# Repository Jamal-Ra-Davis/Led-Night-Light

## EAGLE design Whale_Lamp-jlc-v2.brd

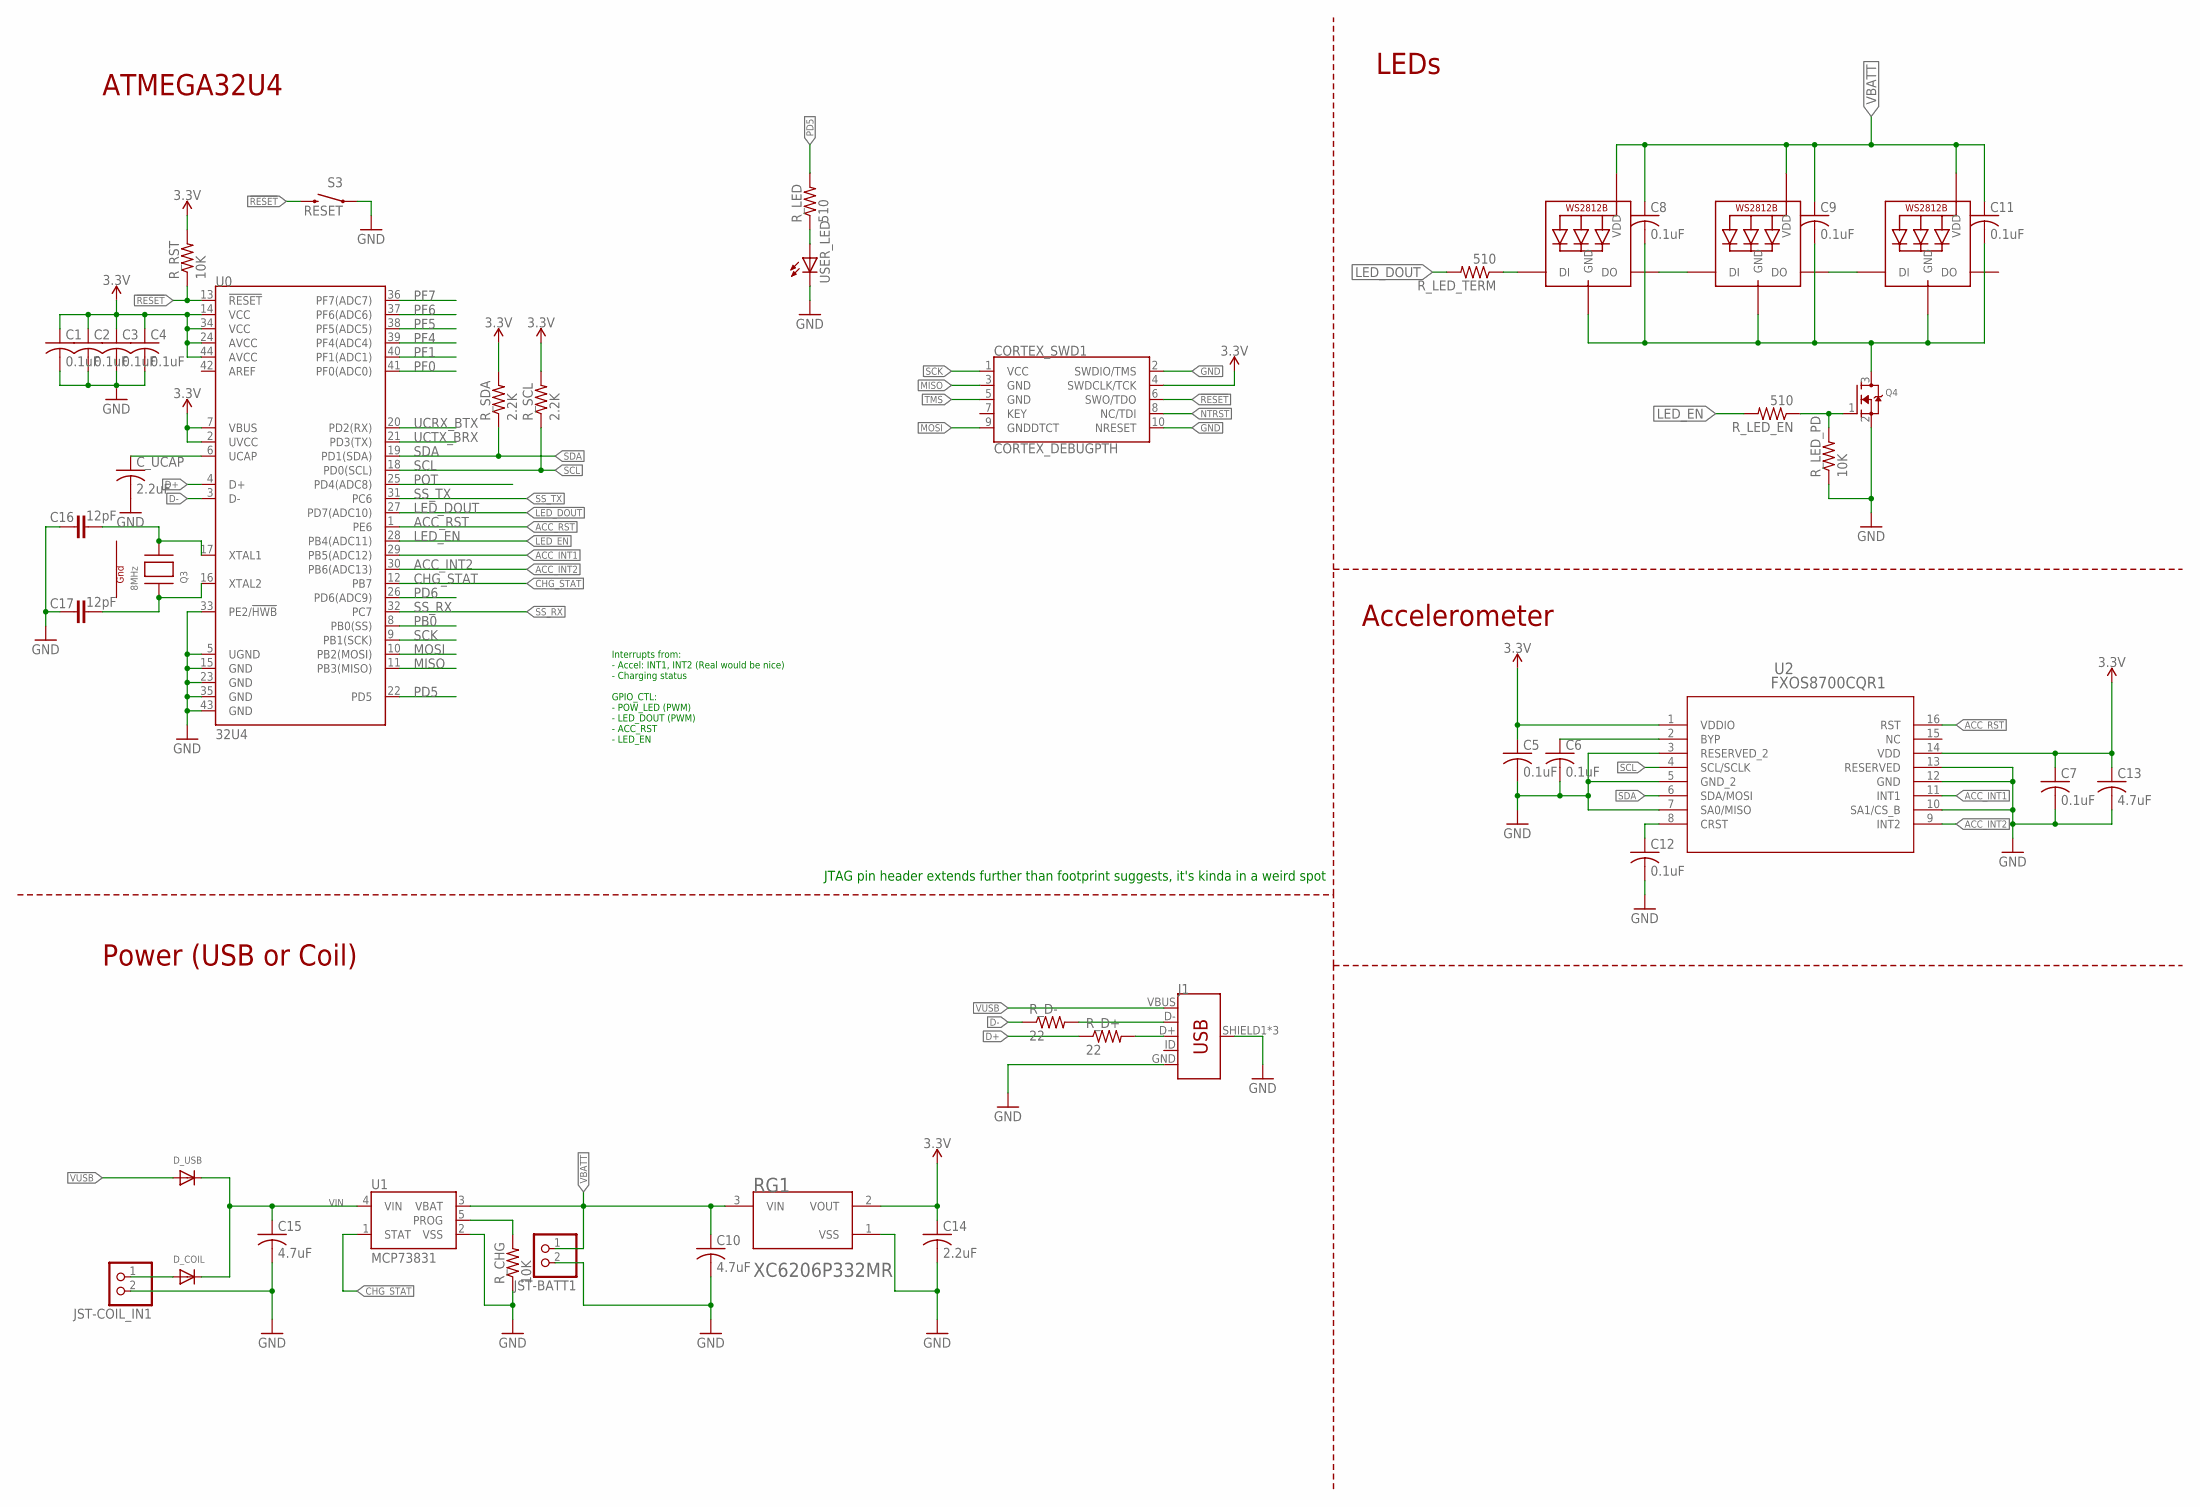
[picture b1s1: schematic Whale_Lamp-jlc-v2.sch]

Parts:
C1, C2, C3, C4, C5, C6, C7, C8, C9, C11, C12: 0.1uF; C0402
C10, C13, C15: 4.7uF; C0603
C14: 2.2uF; C0603
C16, C17: 12pF; 0402-CAP
CORTEX_SWD1: CORTEX_DEBUGPTH; 2X5-PTH-1.27MM
C_UCAP: 2.2uF; C0603
D_COIL: DIODESOD-123; SOD-123
D_USB: DIODESOD-123; SOD-123
J1: USB_MICRO-B_FEMALE-SMT; USB-B-MICRO-SMD
JST-BATT1: JST_2PIN-THM-RA; JST-PH-2-THM-RA
JST-COIL_IN1: JST_2PIN-THM-RA; JST-PH-2-THM-RA
LED1, LED2, LED3: WS2812B3535; LED3535
Q3: 8MHz; NX3225
Q4: MOSFET-NREFLOW; SOT23
RG1: TOREX_XC6206P332MRTOREX_XC6206P332MR_0_0; TOREX_XC6206P332MR_0
R_CHG: 10K; R0402
R_D+: 22; R0402
R_D-: 22; R0402
R_LED: 510; R0402
R_LED_EN: 510; R0402
R_LED_PD: 10K; R0402
R_LED_TERM: 510; R0402
R_RST: 10K; R0402
R_SCL: 2.2K; R0402
R_SDA: 2.2K; R0402
S3: RESET; TACTILE_SWITCH_SMD_4.6X2.8MM
U0: 32U4; QFN-44
U1: MCP73831; SOT23-5
U2: FXOS8700CQR1; QFN16_3X3_NXP
USER_LED: LEDCHIPLED_0603; CHIPLED_0603

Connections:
3.3V: C1.1, C2.1, C3.1, C4.1, C5.1, C7.1, C13.1, C14.1, CORTEX_SWD1.4 (SWDCLK/TCK), RG1.2 (VOUT), R_RST.2, R_SCL.2, R_SDA.2, U0.2 (UVCC), U0.7 (VBUS), U0.14 (VCC), U0.24 (AVCC), U0.34 (VCC), U0.44 (AVCC), U2.1 (VDDIO), U2.14 (VDD)
!RESET: CORTEX_SWD1.6 (SWO/TDO), R_RST.1, S3.3 (2), S3.4 (2), U0.13 (!RESET)
ACC_INT1: U0.29 (PB5(ADC12)), U2.11 (INT1)
ACC_INT2: U0.30 (PB6(ADC13)), U2.9 (INT2)
ACC_RST: U0.1 (PE6), U2.16 (RST)
CHG_STAT: U0.12 (PB7), U1.1 (STAT)
D+: R_D+.1, U0.4 (D+)
D-: R_D-.1, U0.3 (D-)
G1: Q3.4 (G1)
G2: Q3.2 (G2)
GND: C1.2, C2.2, C3.2, C4.2, C5.2, C6.2, C7.2, C10.2, C12.2, C13.2, C14.2, C15.2, C16.1, C17.1, CORTEX_SWD1.2 (SWDIO/TMS), CORTEX_SWD1.10 (NRESET), C_UCAP.2, J1.GND, J1.SHIELD1 (SHIELD), J1.SHIELD2 (SHIELD), J1.SHIELD3 (SHIELD), JST-BATT1.2 (1), JST-COIL_IN1.2 (1), Q4.2 (S), RG1.1 (VSS), R_CHG.1, R_LED_PD.1, S3.1, S3.2 (1), U0.5 (UGND), U0.15 (GND), U0.23 (GND), U0.33 (PE2/!HWB), U0.35 (GND), U0.43 (GND), U1.2 (VSS), U2.3 (RESERVED_2), U2.5 (GND_2), U2.7 (SA0/MISO), U2.10 (SA1/CS_B), U2.12 (GND), U2.13 (RESERVED), USER_LED.C
LED_DOUT: R_LED_TERM.2, U0.27 (PD7(ADC10))
LED_EN: R_LED_EN.2, U0.28 (PB4(ADC11))
MISO: CORTEX_SWD1.3 (GND), U0.11 (PB3(MISO))
MOSI: CORTEX_SWD1.9 (GNDDTCT), U0.10 (PB2(MOSI))
unnamed: J1.D-, R_D-.2
unnamed: R_CHG.2, U1.5 (PROG)
unnamed: R_LED.1, USER_LED.A
unnamed: C16.2, Q3.3 (X2), U0.17 (XTAL1)
unnamed: C17.2, Q3.1 (X1), U0.16 (XTAL2)
unnamed: LED1.3 (DO), LED2.1 (DI)
unnamed: LED2.3 (DO), LED3.1 (DI)
unnamed: C8.2, C9.2, C11.2, LED1.4 (GND), LED2.4 (GND), LED3.4 (GND), Q4.3 (D)
unnamed: LED1.1 (DI), R_LED_TERM.1
unnamed: Q4.1 (G), R_LED_EN.1, R_LED_PD.2
unnamed: C12.1, U2.8 (CRST)
unnamed: C6.1, U2.2 (BYP)
unnamed: C_UCAP.1, U0.6 (UCAP)
unnamed: J1.D+, R_D+.2
unnamed: D_COIL.A, JST-COIL_IN1.1 (2)
NTRST: CORTEX_SWD1.8 (NC/TDI)
PB0: U0.8 (PB0(SS))
PD5: R_LED.2, U0.22 (PD5)
PD6: U0.26 (PD6(ADC9))
PF0: U0.41 (PF0(ADC0))
PF1: U0.40 (PF1(ADC1))
PF4: U0.39 (PF4(ADC4))
PF5: U0.38 (PF5(ADC5))
PF6: U0.37 (PF6(ADC6))
PF7: U0.36 (PF7(ADC7))
POT: U0.25 (PD4(ADC8))
SCK: CORTEX_SWD1.1 (VCC), U0.9 (PB1(SCK))
SCL: R_SCL.1, U0.18 (PD0(SCL)), U2.4 (SCL/SCLK)
SDA: R_SDA.1, U0.19 (PD1(SDA)), U2.6 (SDA/MOSI)
SS_RX: U0.32 (PC7)
SS_TX: U0.31 (PC6)
TMS: CORTEX_SWD1.5 (GND)
UCRX_BTX: U0.20 (PD2(RX))
UCTX_BRX: U0.21 (PD3(TX))
VBATT: C8.1, C9.1, C10.1, C11.1, JST-BATT1.1 (2), LED1.2 (VDD), LED2.2 (VDD), LED3.2 (VDD), RG1.3 (VIN), U1.3 (VBAT)
VIN: C15.1, D_COIL.C, D_USB.C, U1.4 (VIN)
VUSB: D_USB.A, J1.VBUS

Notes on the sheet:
LEDs
ATMEGA32U4
Power (USB or Coil)
Accelerometer
JTAG pin header extends further than footprint suggests, it's kinda in a weird spot
Interrupts from: - Accel: INT1, INT2 (Real would be nice) - Charging status GPIO_CTL: - POW_LED (PWM) - LED_DOUT (PWM) - ACC_RST - LED_EN

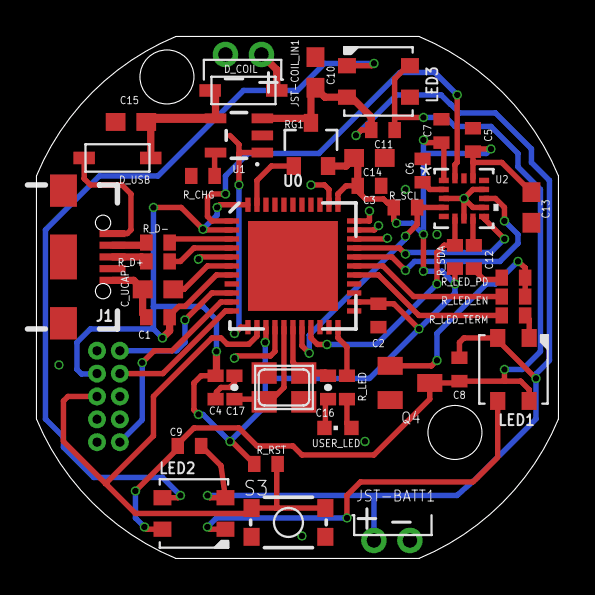
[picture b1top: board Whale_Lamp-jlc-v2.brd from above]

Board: 2 copper layers, 29.0 x 29.0 mm, 45 parts (1 on the bottom side), 35 nets.

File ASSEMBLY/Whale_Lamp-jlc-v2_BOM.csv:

Designator,Quantity,Value,Footprint,LCSC Part #
"D_COIL, D_USB",2,,SOD-123,C8598
USER_LED,1,,603,C72038 
Q4,1,,SOT-23-3L,C20917
Q3,1,,SMD-3225_4P ,C57131 
"C1, C2, C3, C4, C5, C6, C7, C8, C9, C11, C12",11,0.1uF,402,C1525 
"R_CHG, R_CHG_STAT, R_LED_PD, R_RST",4,10K,402,C25744 
"C16, C17",2,12pF,402,C1547 
"R_SCL, R_SDA",2,2.2K,402,C25879 
"C_UCAP, C14",2,2.2uF,603,C23630 
"R_D+, R_D-",2,22,402,C25092 
U0,1,32U4,QFN-44,C45874 
"C10, C13, C15",3,4.7uF,603,C19666 
"R_LED, R_LED_EN, R_LED_TERM",3,510,402,C25123 
U2,1,FXOS8700CQR1,QFN-16_3.0x3.0x0.5P,C432308 
U1,1,MCP73831,SOT23-5,C424093
RG1,1,TOREX_XC6206P332MRTOREX_XC6206P332MR_0_0,SOT-23-3L,C5446
"LED1, LED2, LED3",3,WS2812B3535,LED-4_3535,-

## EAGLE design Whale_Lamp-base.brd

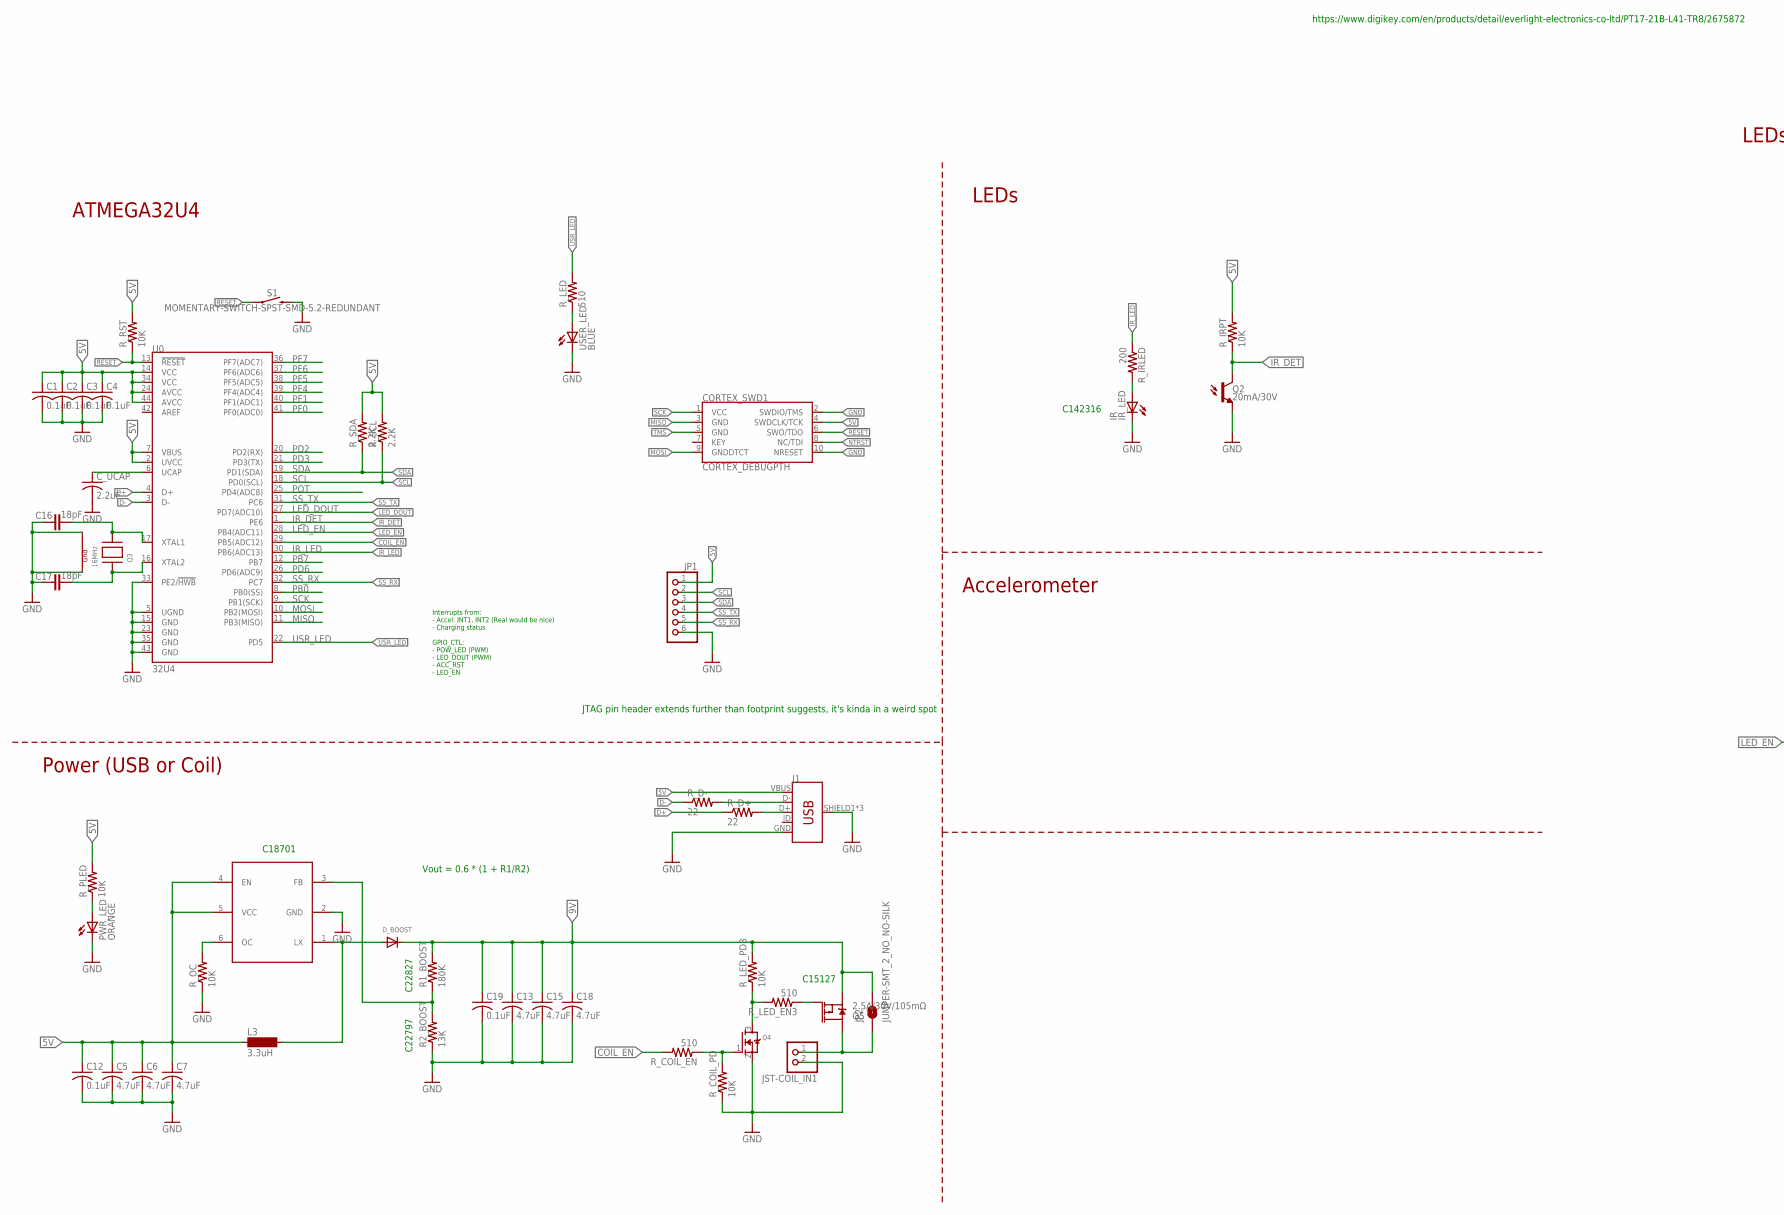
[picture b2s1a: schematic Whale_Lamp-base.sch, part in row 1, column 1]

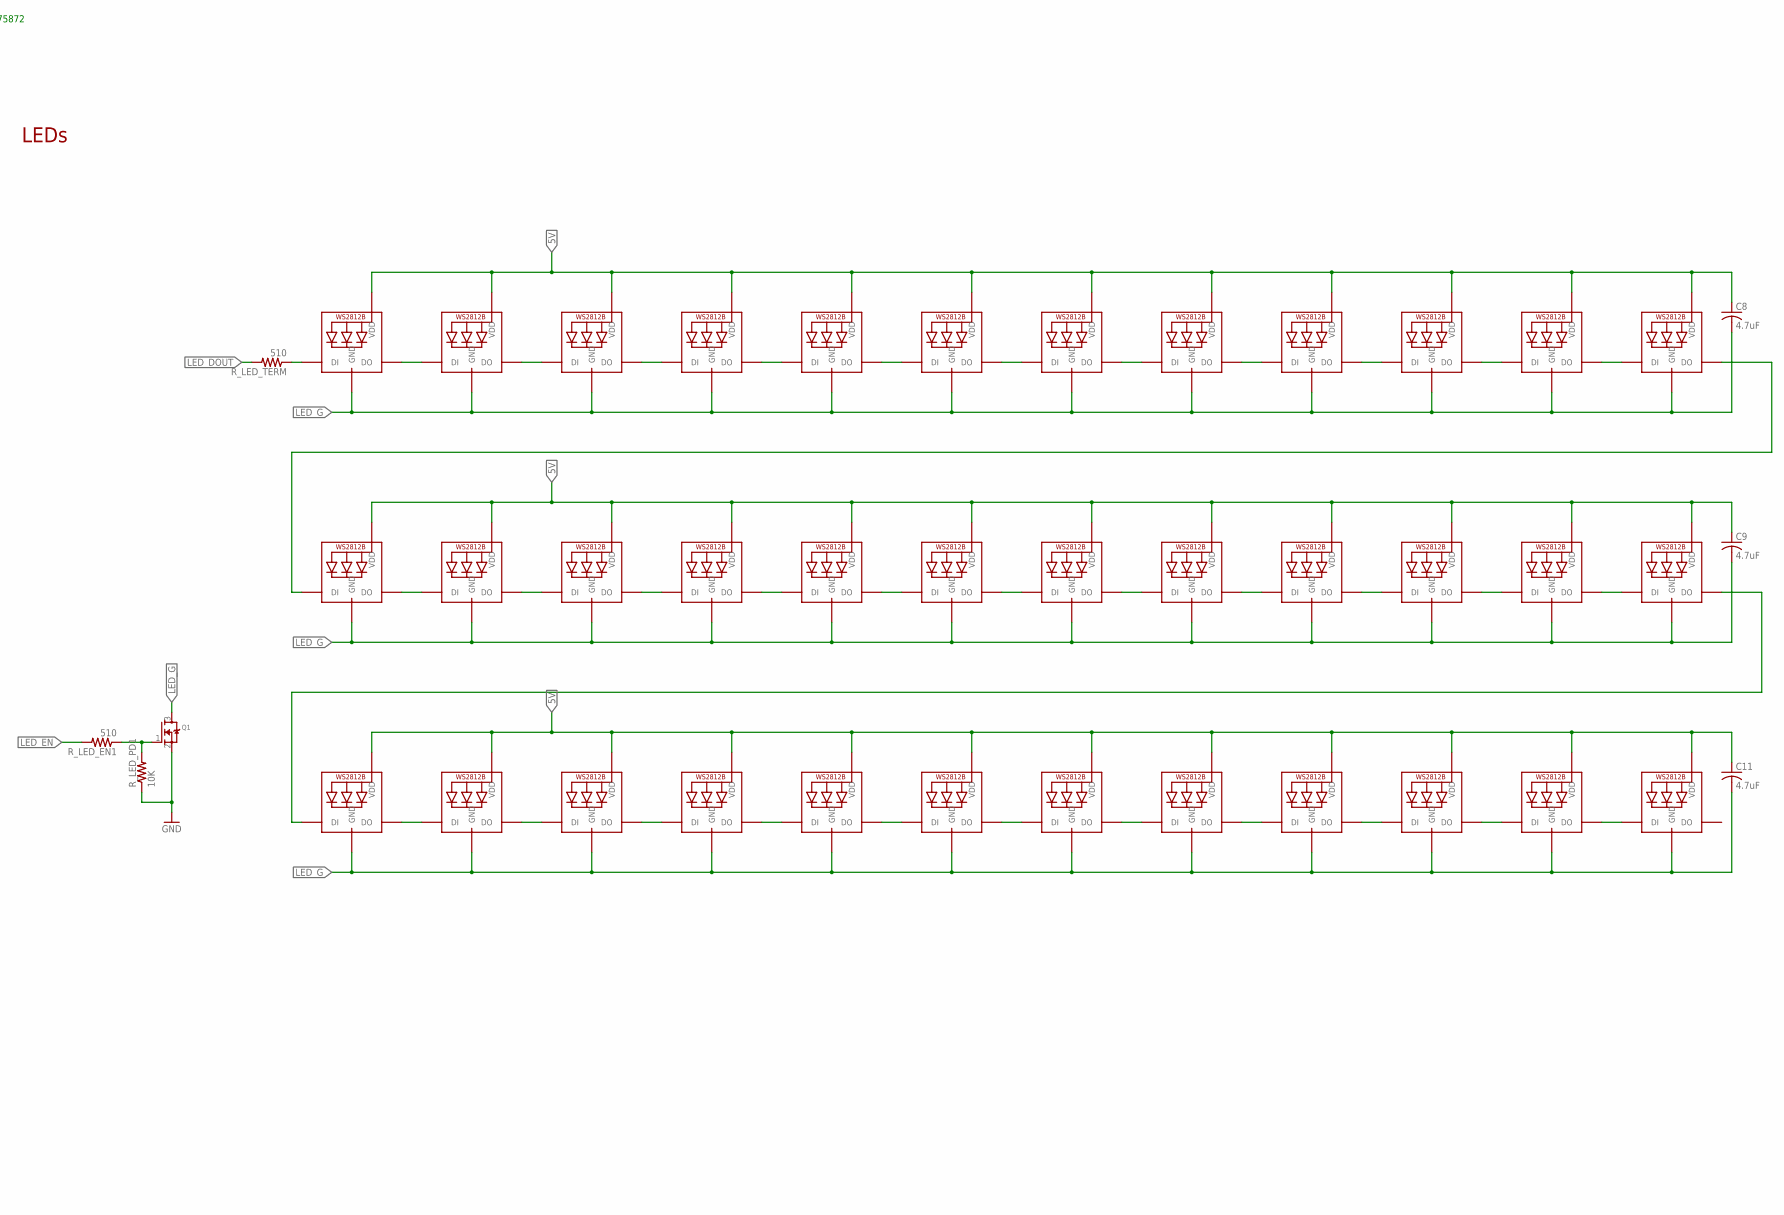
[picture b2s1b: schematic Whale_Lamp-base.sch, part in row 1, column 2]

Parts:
C1, C2, C3, C4, C12, C19: 0.1uF; C0402
C5, C6, C7, C8, C9, C11, C13, C15, C18: 4.7uF; C0603
C16, C17: 18pF; 0402-CAP
CORTEX_SWD1: CORTEX_DEBUGPTH; 2X5-PTH-1.27MM
C_UCAP: 2.2uF; C0603
D_BOOST: DIODESOD-123; SOD-123
FP6291: FP6291; SOT23-6L
IR_LED: IR; CHIPLED_0603
J1: USB_MICRO-B_FEMALE-SMT; USB-B-MICRO-SMD
JP1: PINHD-1X6; 1X06
JP2: JUMPER-SMT_2_NO_NO-SILK; SMT-JUMPER_2_NO_NO-SILK
JST-COIL_IN1: JST_2PIN-THM-RA; JST-PH-2-THM-RA
L3: 3.3uH; MS50
LED1, LED2, LED3, LED4, LED5, LED6, LED7, LED8, LED9, LED10, LED11, LED12, LED13, LED14, LED15, LED16, LED17, LED18, LED19, LED20, LED21, LED22, LED23, LED24, LED25, LED26, LED27, LED28, LED29, LED30, LED31, LED32, LED33, LED34, LED35, LED36: WS2812B_5050N; WS2812B-NARROW
PWR_LED: ORANGE; CHIPLED_0603
Q1, Q4: MOSFET-NREFLOW; SOT23
Q2: 20mA/30V; PT17-21C-L41-TR8
Q3: 16MHz; NX3225
Q5: 2.5A/30V/105mΩ; SOT23-3
R1_BOOST: 180K; R0603
R2_BOOST: 13K; R0603
R_COIL_EN: 510; R0402
R_COIL_PD: 10K; R0402
R_D+: 22; R0402
R_D-: 22; R0402
R_IRLED: 200; R0603
R_IRPT: 10K; R0402
R_LED: 510; R0402
R_LED_EN1, R_LED_EN3: 510; R0402
R_LED_PD1, R_LED_PD3: 10K; R0402
R_LED_TERM: 510; R0402
R_OC: 10K; R0402
R_PLED: 10K; R0402
R_RST: 10K; R0402
R_SCL: 2.2K; R0402
R_SDA: 2.2K; R0402
S1: MOMENTARY-SWITCH-SPST-SMD-5.2-REDUNDANT; TACTILE_SWITCH_SMD_5.2MM
U0: 32U4; QFN-44
USER_LED: BLUE; CHIPLED_0603

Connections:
5V: C1.1, C2.1, C3.1, C4.1, C5.1, C6.1, C7.1, C8.1, C9.1, C11.1, C12.1, CORTEX_SWD1.4 (SWDCLK/TCK), FP6291.4 (EN), FP6291.5 (VCC), J1.VBUS, JP1.1, L3.1, LED1.1-VDD (VDD), LED2.1-VDD (VDD), LED3.1-VDD (VDD), LED4.1-VDD (VDD), LED5.1-VDD (VDD), LED6.1-VDD (VDD), LED7.1-VDD (VDD), LED8.1-VDD (VDD), LED9.1-VDD (VDD), LED10.1-VDD (VDD), LED11.1-VDD (VDD), LED12.1-VDD (VDD), LED13.1-VDD (VDD), LED14.1-VDD (VDD), LED15.1-VDD (VDD), LED16.1-VDD (VDD), LED17.1-VDD (VDD), LED18.1-VDD (VDD), LED19.1-VDD (VDD), LED20.1-VDD (VDD), LED21.1-VDD (VDD), LED22.1-VDD (VDD), LED23.1-VDD (VDD), LED24.1-VDD (VDD), LED25.1-VDD (VDD), LED26.1-VDD (VDD), LED27.1-VDD (VDD), LED28.1-VDD (VDD), LED29.1-VDD (VDD), LED30.1-VDD (VDD), LED31.1-VDD (VDD), LED32.1-VDD (VDD), LED33.1-VDD (VDD), LED34.1-VDD (VDD), LED35.1-VDD (VDD), LED36.1-VDD (VDD), R_IRPT.2, R_PLED.2, R_RST.2, R_SCL.2, R_SDA.2, U0.2 (UVCC), U0.7 (VBUS), U0.14 (VCC), U0.24 (AVCC), U0.34 (VCC), U0.44 (AVCC)
9V: C13.1, C15.1, C18.1, C19.1, D_BOOST.C, JP2.2, Q5.2 (S), R1_BOOST.2, R_LED_PD3.2
!RESET: CORTEX_SWD1.6 (SWO/TDO), R_RST.1, S1.1, S1.2 (1), U0.13 (!RESET)
COIL_EN: R_COIL_EN.2, U0.29 (PB5(ADC12))
D+: R_D+.1, U0.4 (D+)
D-: R_D-.1, U0.3 (D-)
GND: C1.2, C2.2, C3.2, C4.2, C5.2, C6.2, C7.2, C12.2, C13.2, C15.2, C16.1, C17.1, C18.2, C19.2, CORTEX_SWD1.2 (SWDIO/TMS), CORTEX_SWD1.10 (NRESET), C_UCAP.2, FP6291.2 (GND), IR_LED.C, J1.GND, J1.SHIELD1 (SHIELD), J1.SHIELD2 (SHIELD), J1.SHIELD3 (SHIELD), JP1.6, JST-COIL_IN1.2 (1), PWR_LED.C, Q1.2 (S), Q2.E, Q3.2 (G2), Q3.4 (G1), Q4.2 (S), R2_BOOST.1, R_COIL_PD.1, R_LED_PD1.1, R_OC.1, S1.3 (2), S1.4 (2), U0.5 (UGND), U0.15 (GND), U0.23 (GND), U0.33 (PE2/!HWB), U0.35 (GND), U0.43 (GND), USER_LED.C
IR_DET: Q2.C, R_IRPT.1, U0.1 (PE6)
IR_LED: R_IRLED.1, U0.30 (PB6(ADC13))
LED_DOUT: R_LED_TERM.2, U0.27 (PD7(ADC10))
LED_EN: R_LED_EN1.2, U0.28 (PB4(ADC11))
LED_G: C8.2, C9.2, C11.2, LED1.3-GND (GND), LED2.3-GND (GND), LED3.3-GND (GND), LED4.3-GND (GND), LED5.3-GND (GND), LED6.3-GND (GND), LED7.3-GND (GND), LED8.3-GND (GND), LED9.3-GND (GND), LED10.3-GND (GND), LED11.3-GND (GND), LED12.3-GND (GND), LED13.3-GND (GND), LED14.3-GND (GND), LED15.3-GND (GND), LED16.3-GND (GND), LED17.3-GND (GND), LED18.3-GND (GND), LED19.3-GND (GND), LED20.3-GND (GND), LED21.3-GND (GND), LED22.3-GND (GND), LED23.3-GND (GND), LED24.3-GND (GND), LED25.3-GND (GND), LED26.3-GND (GND), LED27.3-GND (GND), LED28.3-GND (GND), LED29.3-GND (GND), LED30.3-GND (GND), LED31.3-GND (GND), LED32.3-GND (GND), LED33.3-GND (GND), LED34.3-GND (GND), LED35.3-GND (GND), LED36.3-GND (GND), Q1.3 (D)
MISO: CORTEX_SWD1.3 (GND), U0.11 (PB3(MISO))
MOSI: CORTEX_SWD1.9 (GNDDTCT), U0.10 (PB2(MOSI))
unnamed: LED1.2-DOUT (DO), LED2.4-DIN (DI)
unnamed: LED4.2-DOUT (DO), LED5.4-DIN (DI)
unnamed: LED5.2-DOUT (DO), LED6.4-DIN (DI)
unnamed: LED7.2-DOUT (DO), LED8.4-DIN (DI)
unnamed: LED8.2-DOUT (DO), LED9.4-DIN (DI)
unnamed: Q4.1 (G), R_COIL_EN.1, R_COIL_PD.2
unnamed: R_LED.1, USER_LED.A
unnamed: LED13.2-DOUT (DO), LED14.4-DIN (DI)
unnamed: C16.2, Q3.3 (X2), U0.17 (XTAL1)
unnamed: C17.2, Q3.1 (X1), U0.16 (XTAL2)
unnamed: LED14.2-DOUT (DO), LED15.4-DIN (DI)
unnamed: LED12.2-DOUT (DO), LED13.4-DIN (DI)
unnamed: LED16.2-DOUT (DO), LED17.4-DIN (DI)
unnamed: LED17.2-DOUT (DO), LED18.4-DIN (DI)
unnamed: LED19.2-DOUT (DO), LED20.4-DIN (DI)
unnamed: LED20.2-DOUT (DO), LED21.4-DIN (DI)
unnamed: LED21.2-DOUT (DO), LED22.4-DIN (DI)
unnamed: Q5.1 (G), R_LED_EN3.1
unnamed: LED22.2-DOUT (DO), LED23.4-DIN (DI)
unnamed: C_UCAP.1, U0.6 (UCAP)
unnamed: LED23.2-DOUT (DO), LED24.4-DIN (DI)
unnamed: LED15.2-DOUT (DO), LED16.4-DIN (DI)
unnamed: PWR_LED.A, R_PLED.1
unnamed: LED18.2-DOUT (DO), LED19.4-DIN (DI)
unnamed: LED25.2-DOUT (DO), LED26.4-DIN (DI)
unnamed: LED26.2-DOUT (DO), LED27.4-DIN (DI)
unnamed: LED24.2-DOUT (DO), LED25.4-DIN (DI)
unnamed: LED28.2-DOUT (DO), LED29.4-DIN (DI)
unnamed: LED29.2-DOUT (DO), LED30.4-DIN (DI)
unnamed: LED31.2-DOUT (DO), LED32.4-DIN (DI)
unnamed: LED32.2-DOUT (DO), LED33.4-DIN (DI)
unnamed: LED34.2-DOUT (DO), LED35.4-DIN (DI)
unnamed: LED2.2-DOUT (DO), LED3.4-DIN (DI)
unnamed: LED35.2-DOUT (DO), LED36.4-DIN (DI)
unnamed: LED27.2-DOUT (DO), LED28.4-DIN (DI)
unnamed: LED30.2-DOUT (DO), LED31.4-DIN (DI)
unnamed: Q1.1 (G), R_LED_EN1.1, R_LED_PD1.2
unnamed: LED1.4-DIN (DI), R_LED_TERM.1
unnamed: LED10.2-DOUT (DO), LED11.4-DIN (DI)
unnamed: LED11.2-DOUT (DO), LED12.4-DIN (DI)
unnamed: JP2.1, JST-COIL_IN1.1 (2), Q5.3 (D)
unnamed: LED3.2-DOUT (DO), LED4.4-DIN (DI)
unnamed: LED6.2-DOUT (DO), LED7.4-DIN (DI)
unnamed: IR_LED.A, R_IRLED.2
unnamed: LED33.2-DOUT (DO), LED34.4-DIN (DI)
unnamed: FP6291.6 (OC), R_OC.2
unnamed: J1.D-, R_D-.2
unnamed: D_BOOST.A, FP6291.1 (LX), L3.2
unnamed: J1.D+, R_D+.2
unnamed: FP6291.3 (FB), R1_BOOST.1, R2_BOOST.2
unnamed: LED9.2-DOUT (DO), LED10.4-DIN (DI)
NTRST: CORTEX_SWD1.8 (NC/TDI)
PB0: U0.8 (PB0(SS))
PB7: U0.12 (PB7)
PCH_GATE: Q4.3 (D), R_LED_EN3.2, R_LED_PD3.1
PD2: U0.20 (PD2(RX))
PD3: U0.21 (PD3(TX))
PD6: U0.26 (PD6(ADC9))
PF0: U0.41 (PF0(ADC0))
PF1: U0.40 (PF1(ADC1))
PF4: U0.39 (PF4(ADC4))
PF5: U0.38 (PF5(ADC5))
PF6: U0.37 (PF6(ADC6))
PF7: U0.36 (PF7(ADC7))
POT: U0.25 (PD4(ADC8))
SCK: CORTEX_SWD1.1 (VCC), U0.9 (PB1(SCK))
SCL: JP1.2, R_SCL.1, U0.18 (PD0(SCL))
SDA: JP1.3, R_SDA.1, U0.19 (PD1(SDA))
SS_RX: JP1.5, U0.32 (PC7)
SS_TX: JP1.4, U0.31 (PC6)
TMS: CORTEX_SWD1.5 (GND)
USR_LED: R_LED.2, U0.22 (PD5)

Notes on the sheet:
LEDs
ATMEGA32U4
Power (USB or Coil)
Accelerometer
JTAG pin header extends further than footprint suggests, it's kinda in a weird spot
Interrupts from: - Accel: INT1, INT2 (Real would be nice) - Charging status GPIO_CTL: - POW_LED (PWM) - LED_DOUT (PWM) - ACC_RST - LED_EN
C15127
https://www.digikey.com/en/products/detail/everlight-electronics-co-ltd/PT17-21B-L41-TR8/2675872
C142316
C18701
Vout = 0.6 * (1 + R1/R2)
C22797
C22827

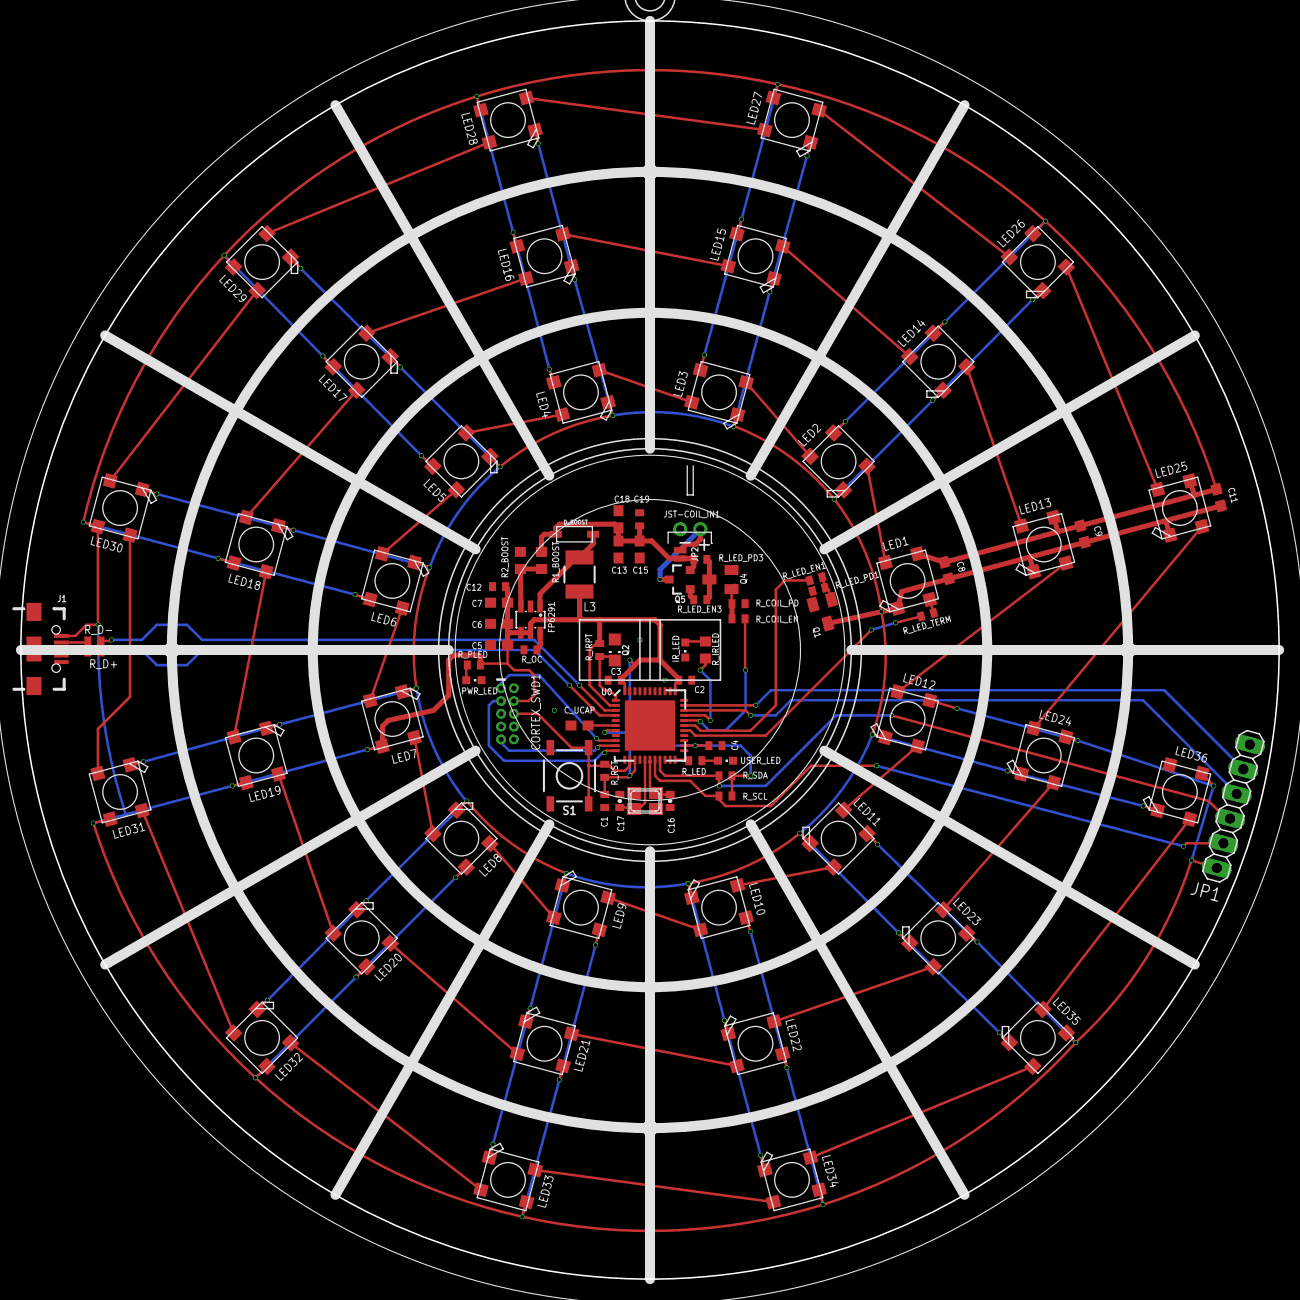
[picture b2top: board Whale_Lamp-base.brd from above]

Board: 2 copper layers, 125.0 x 125.0 mm, 91 parts (0 on the bottom side), 72 nets.

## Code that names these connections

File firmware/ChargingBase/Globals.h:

#ifndef GLOBALS_LIB_
#define GLOBALS_LIB_

#define LED_DOUT  6
#define IR_DET    7
#define LED_EN    8
#define COIL_EN   9
#define IR_LED    10

void set_user_led(bool on)
{
  if (on)
    PORTD |= (1 << PD5);
  else
    PORTD &= ~(1 << PD5);
}

#endif

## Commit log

2020-11-21 finished board layout
2020-11-22 Silkscreen cleanup and added additional info into schematic
2020-11-22 Added labels to ext header
2020-11-23 added assembly files
2020-11-23 Added gerber zip file
2020-11-30 JLC_Order_11-24-2020
2020-12-02 added start of firmware for charging base
2020-12-03 Added new animations and organized animations into classes
2020-12-05 Added mechanical directory to store stls for charging base
2020-12-06 Added snake animation

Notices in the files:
parts and their libraries:
SparkFun-IC-Microcontroller: Licensing: Creative Commons ShareAlike 4.0 International - https://creativecommons.org/licenses/by-sa/4.0
COPYRIGHT: Copyright (C) 2018 Accelerated Designs. All rights reserved
